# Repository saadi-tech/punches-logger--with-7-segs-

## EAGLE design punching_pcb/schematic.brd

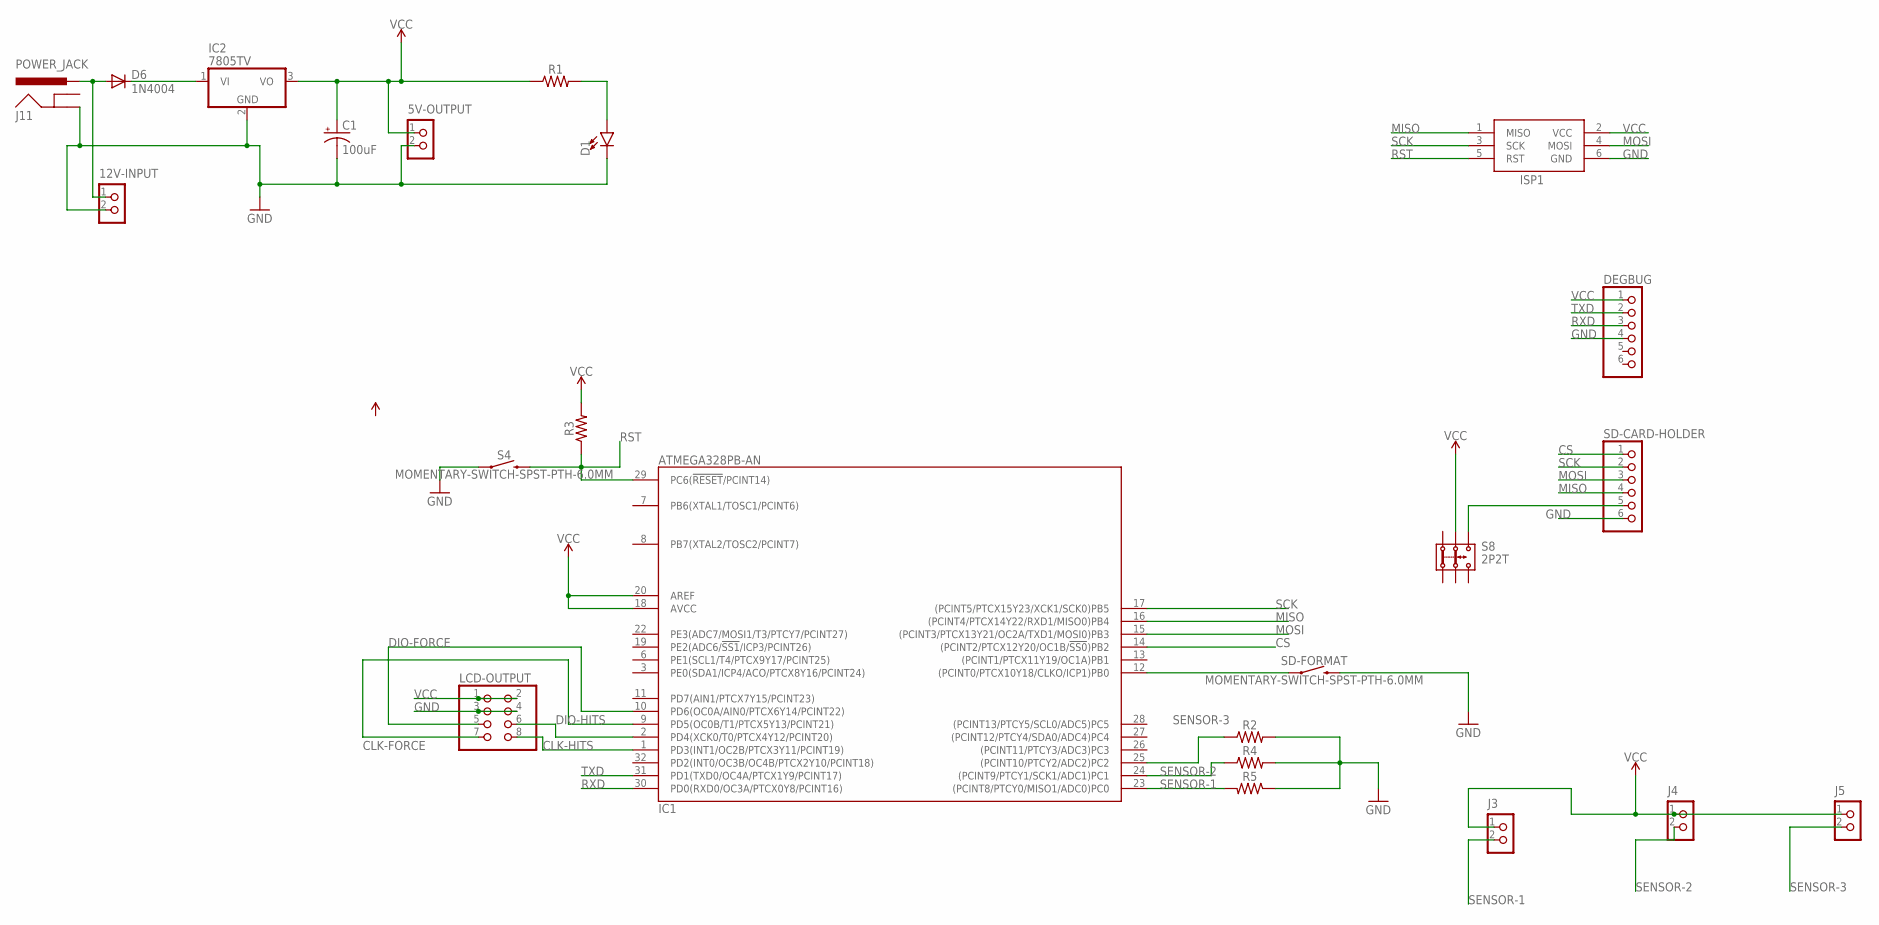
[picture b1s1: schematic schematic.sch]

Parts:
5V-OUTPUT, 12V-INPUT: CON_TERMINAL_BLOCK_02-5MM; TERMINAL_BLOCK_2P_5
C1: 100uF; CPOL-RADIAL-2.5MM-6.5MM
D1: LED1206; LED-1206
D6: 1N4004; DO41-10
DEGBUG: PINHD-1X6; 1X06
IC1: ATMEGA328PB-AN; QFP32_7X7_0.80
IC2: 7805TV; TO220V
ISP1: AVRISP-6; AVRISP
J3, J4, J5: CON_TERMINAL_BLOCK_02-5MM; TERMINAL_BLOCK_2P_5
J11: POWER_JACK; POWER_JACK_PTH
LCD-OUTPUT: PINHD-2X4; 2X04
R1, R2, R3, R4, R5: 1206
S4: MOMENTARY-SWITCH-SPST-PTH-6.0MM; TACTILE_SWITCH_PTH_6.0MM
S8: 2P2T
SD-CARD-HOLDER: PINHD-1X6; 1X06
SD-FORMAT: MOMENTARY-SWITCH-SPST-PTH-6.0MM; TACTILE_SWITCH_PTH_6.0MM

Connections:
CLK-FORCE: IC1.9 (PD5(OC0B/T1/PTCX5Y13/PCINT21)), LCD-OUTPUT.7
CLK-HITS: IC1.1 (PD3(INT1/OC2B/PTCX3Y11/PCINT19)), LCD-OUTPUT.8
CS: IC1.14 ((PCINT2/PTCX12Y20/OC1B/!SS0!)PB2), SD-CARD-HOLDER.1
DIO-FORCE: IC1.10 (PD6(OC0A/AIN0/PTCX6Y14/PCINT22)), LCD-OUTPUT.5
DIO-HITS: IC1.2 (PD4(XCK0/T0/PTCX4Y12/PCINT20)), LCD-OUTPUT.6
GND: 5V-OUTPUT.2, 12V-INPUT.2, C1.2 (-), D1.C, DEGBUG.4, IC1.5 (GND), IC1.21 (GND), IC2.2 (GND), ISP1.6 (GND), J11.GND, LCD-OUTPUT.3, LCD-OUTPUT.4, R2.2, R4.2, R5.1, S4.1, SD-CARD-HOLDER.6, SD-FORMAT.3 (2)
MISO: IC1.16 ((PCINT4/PTCX14Y22/RXD1/MISO0)PB4), ISP1.1 (MISO), SD-CARD-HOLDER.4
MOSI: IC1.15 ((PCINT3/PTCX13Y21/OC2A/TXD1/MOSI0)PB3), ISP1.4 (MOSI), SD-CARD-HOLDER.3
unnamed: D1.A, R1.2
unnamed: IC1.12 ((PCINT0/PTCX10Y18/CLKO/ICP1)PB0), SD-FORMAT.1
unnamed: 12V-INPUT.1, D6.A, J11.PWR
unnamed: D6.C, IC2.1 (VI)
unnamed: S8.3.1, SD-CARD-HOLDER.5
RST: IC1.29 (PC6(!RESET!/PCINT14)), ISP1.5 (RST), R3.1, S4.3 (2)
RXD: DEGBUG.3, IC1.30 (PD0(RXD0/OC3A/PTCX0Y8/PCINT16))
SCK: IC1.17 ((PCINT5/PTCX15Y23/XCK1/SCK0)PB5), ISP1.3 (SCK), SD-CARD-HOLDER.2
SENSOR-1: IC1.23 ((PCINT8/PTCY0/MISO1/ADC0)PC0), J3.2, R5.2
SENSOR-2: IC1.24 ((PCINT9/PTCY1/SCK1/ADC1)PC1), J4.2, R4.1
SENSOR-3: IC1.25 ((PCINT10/PTCY2/ADC2)PC2), J5.2, R2.1
TXD: DEGBUG.2, IC1.31 (PD1(TXD0/OC4A/PTCX1Y9/PCINT17))
VCC: 5V-OUTPUT.1, C1.1 (+), DEGBUG.1, IC1.4 (VCC), IC1.18 (AVCC), IC1.20 (AREF), IC2.3 (VO), ISP1.2 (VCC), J3.1, J4.1, J5.1, LCD-OUTPUT.1, LCD-OUTPUT.2, R1.1, R3.2, S8.2.1

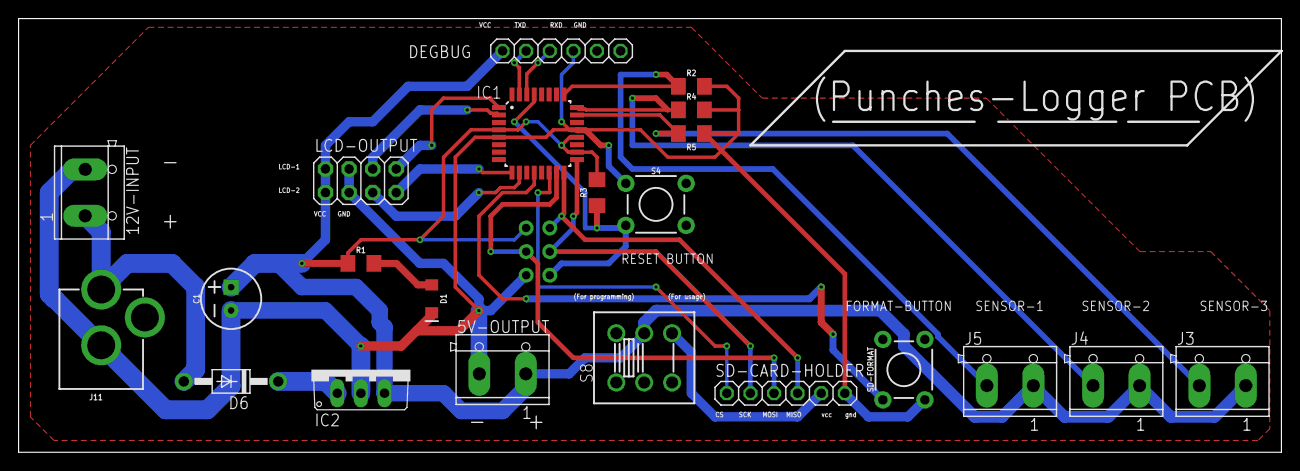
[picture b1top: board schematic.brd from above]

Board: 2 copper layers, 135.9 x 46.7 mm, 23 parts (1 on the bottom side), 21 nets.

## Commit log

2020-10-31 this is my first comit

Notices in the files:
parts and their libraries:
SparkFun-Capacitors: Licensing: Creative Commons ShareAlike 4.0 International - https://creativecommons.org/licenses/by-sa/4.0
